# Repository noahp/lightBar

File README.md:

# lightBar
  
Basic serial addressable WS2812B RGB LED banner. Comprised of multiple 12x7 modules.

# hardware
Ordered the boards from dirtypcbs.com, $25 shipped. I received 11 boards (1 bonus!), 22 days turn, pretty nice.  
The basic module contains 84 LEDs arranged in 7 rows of 12 each, and is designed to display 2 monospaced 5x7 pixel characters.  
Several 2-character modules can be connected together to create the full display.  

## schematic
[pdf view](https://github.com/noahp/lightBar/raw/master/hw/lightBar.pdf)

## pcb renders

# software
My plan is to use some Cortex-M processor on the strip itself to do the real-time LED control (framebuffer + SPI transmission). Probably an ESP8266 wifi module (ESP-12) will be used as the interface for setting the displayed data.  
Some ideas-  
- get internet time/date and display it
- display weather, possibly using a gradient over the text background showing temperature/precip conditions

I'm thinking some simple description language (maybe JSON format) to transmit the content from the ESP8266 to the LED controller. Something that can describe text content and position, bitmaps, maybe transparency. The LED controller would parse this data into its bitmapped frame buffer and print it on the display.

For operation of the ESP8266, flow would be like this-  
`wakeup->connect to saved access point credentials (lua file system)`  
`    ->success, get time and date and weather information->sleep`  
`    ->failure after few seconds, switch to access point mode and serve simple web page form with 2 fields, for ssid + key->if HTTP POSTs new credentials->back to start (try to connect)`

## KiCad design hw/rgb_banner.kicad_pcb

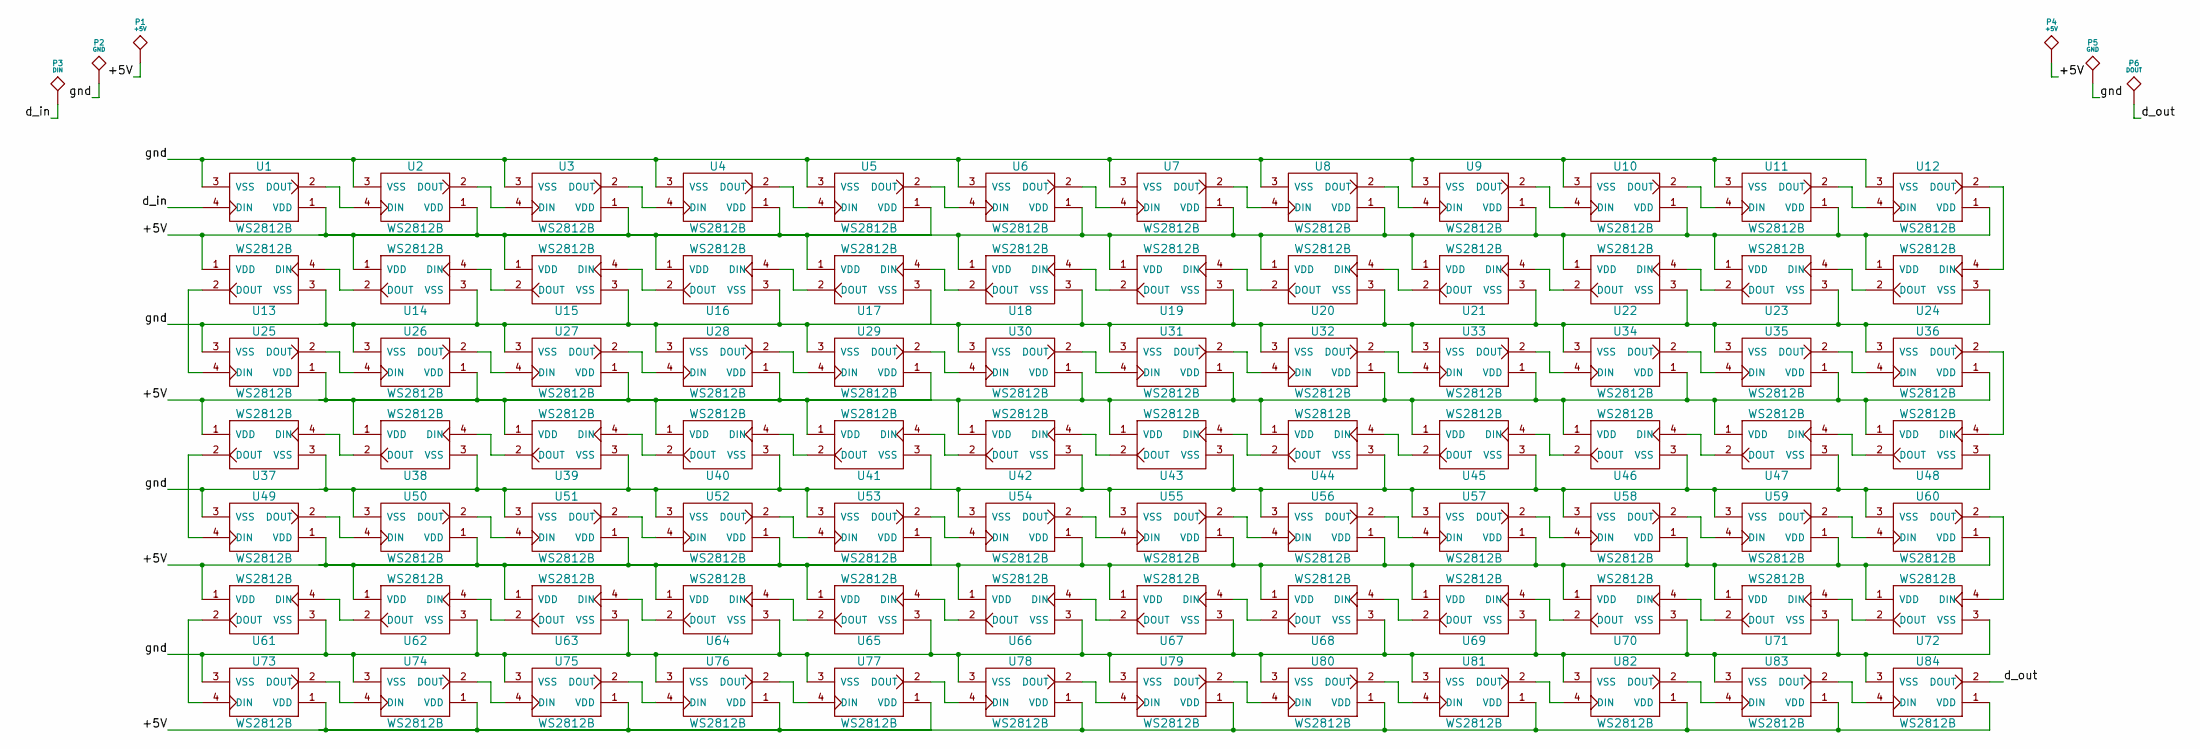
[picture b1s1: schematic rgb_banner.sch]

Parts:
P1, P4: +5V; TEST_0.100
P2, P5: GND; TEST_0.100
P3: DIN; TEST_0.100
P6: DOUT; TEST_0.100
U1, U2, U3, U4, U5, U6, U7, U8, U9, U10, U11, U12, U13, U14, U15, U16, U17, U18, U19, U20, U21, U22, U23, U24, U25, U26, U27, U28, U29, U30, U31, U32, U33, U34, U35, U36, U37, U38, U39, U40, U41, U42, U43, U44, U45, U46, U47, U48, U49, U50, U51, U52, U53, U54, U55, U56, U57, U58, U59, U60, U61, U62, U63, U64, U65, U66, U67, U68, U69, U70, U71, U72, U73, U74, U75, U76, U77, U78, U79, U80, U81, U82, U83, U84: WS2812B; WS2812B_SMD_5050

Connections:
/+5V: P1.1, P4.1, U1.1 (VDD), U2.1 (VDD), U3.1 (VDD), U4.1 (VDD), U5.1 (VDD), U6.1 (VDD), U7.1 (VDD), U8.1 (VDD), U9.1 (VDD), U10.1 (VDD), U11.1 (VDD), U12.1 (VDD), U13.1 (VDD), U14.1 (VDD), U15.1 (VDD), U16.1 (VDD), U17.1 (VDD), U18.1 (VDD), U19.1 (VDD), U20.1 (VDD), U21.1 (VDD), U22.1 (VDD), U23.1 (VDD), U24.1 (VDD), U25.1 (VDD), U26.1 (VDD), U27.1 (VDD), U28.1 (VDD), U29.1 (VDD), U30.1 (VDD), U31.1 (VDD), U32.1 (VDD), U33.1 (VDD), U34.1 (VDD), U35.1 (VDD), U36.1 (VDD), U37.1 (VDD), U38.1 (VDD), U39.1 (VDD), U40.1 (VDD), U41.1 (VDD), U42.1 (VDD), U43.1 (VDD), U44.1 (VDD), U45.1 (VDD), U46.1 (VDD), U47.1 (VDD), U48.1 (VDD), U49.1 (VDD), U50.1 (VDD), U51.1 (VDD), U52.1 (VDD), U53.1 (VDD), U54.1 (VDD), U55.1 (VDD), U56.1 (VDD), U57.1 (VDD), U58.1 (VDD), U59.1 (VDD), U60.1 (VDD), U61.1 (VDD), U62.1 (VDD), U63.1 (VDD), U64.1 (VDD), U65.1 (VDD), U66.1 (VDD), U67.1 (VDD), U68.1 (VDD), U69.1 (VDD), U70.1 (VDD), U71.1 (VDD), U72.1 (VDD), U73.1 (VDD), U74.1 (VDD), U75.1 (VDD), U76.1 (VDD), U77.1 (VDD), U78.1 (VDD), U79.1 (VDD), U80.1 (VDD), U81.1 (VDD), U82.1 (VDD), U83.1 (VDD), U84.1 (VDD)
/d_in: P3.1, U1.4 (DIN)
/d_out: P6.1, U84.2 (DOUT)
/gnd: P2.1, P5.1, U1.3 (VSS), U2.3 (VSS), U3.3 (VSS), U4.3 (VSS), U5.3 (VSS), U6.3 (VSS), U7.3 (VSS), U8.3 (VSS), U9.3 (VSS), U10.3 (VSS), U11.3 (VSS), U12.3 (VSS), U13.3 (VSS), U14.3 (VSS), U15.3 (VSS), U16.3 (VSS), U17.3 (VSS), U18.3 (VSS), U19.3 (VSS), U20.3 (VSS), U21.3 (VSS), U22.3 (VSS), U23.3 (VSS), U24.3 (VSS), U25.3 (VSS), U26.3 (VSS), U27.3 (VSS), U28.3 (VSS), U29.3 (VSS), U30.3 (VSS), U31.3 (VSS), U32.3 (VSS), U33.3 (VSS), U34.3 (VSS), U35.3 (VSS), U36.3 (VSS), U37.3 (VSS), U38.3 (VSS), U39.3 (VSS), U40.3 (VSS), U41.3 (VSS), U42.3 (VSS), U43.3 (VSS), U44.3 (VSS), U45.3 (VSS), U46.3 (VSS), U47.3 (VSS), U48.3 (VSS), U49.3 (VSS), U50.3 (VSS), U51.3 (VSS), U52.3 (VSS), U53.3 (VSS), U54.3 (VSS), U55.3 (VSS), U56.3 (VSS), U57.3 (VSS), U58.3 (VSS), U59.3 (VSS), U60.3 (VSS), U61.3 (VSS), U62.3 (VSS), U63.3 (VSS), U64.3 (VSS), U65.3 (VSS), U66.3 (VSS), U67.3 (VSS), U68.3 (VSS), U69.3 (VSS), U70.3 (VSS), U71.3 (VSS), U72.3 (VSS), U73.3 (VSS), U74.3 (VSS), U75.3 (VSS), U76.3 (VSS), U77.3 (VSS), U78.3 (VSS), U79.3 (VSS), U80.3 (VSS), U81.3 (VSS), U82.3 (VSS), U83.3 (VSS), U84.3 (VSS)
unnamed: U1.2 (DOUT), U2.4 (DIN)
unnamed: U2.2 (DOUT), U3.4 (DIN)
unnamed: U3.2 (DOUT), U4.4 (DIN)
unnamed: U4.2 (DOUT), U5.4 (DIN)
unnamed: U5.2 (DOUT), U6.4 (DIN)
unnamed: U6.2 (DOUT), U7.4 (DIN)
unnamed: U7.2 (DOUT), U8.4 (DIN)
unnamed: U8.2 (DOUT), U9.4 (DIN)
unnamed: U10.2 (DOUT), U11.4 (DIN)
unnamed: U9.2 (DOUT), U10.4 (DIN)
unnamed: U11.2 (DOUT), U12.4 (DIN)
unnamed: U12.2 (DOUT), U24.4 (DIN)
unnamed: U13.2 (DOUT), U25.4 (DIN)
unnamed: U13.4 (DIN), U14.2 (DOUT)
unnamed: U14.4 (DIN), U15.2 (DOUT)
unnamed: U15.4 (DIN), U16.2 (DOUT)
unnamed: U16.4 (DIN), U17.2 (DOUT)
unnamed: U17.4 (DIN), U18.2 (DOUT)
unnamed: U18.4 (DIN), U19.2 (DOUT)
unnamed: U19.4 (DIN), U20.2 (DOUT)
unnamed: U20.4 (DIN), U21.2 (DOUT)
unnamed: U21.4 (DIN), U22.2 (DOUT)
unnamed: U22.4 (DIN), U23.2 (DOUT)
unnamed: U23.4 (DIN), U24.2 (DOUT)
unnamed: U25.2 (DOUT), U26.4 (DIN)
unnamed: U26.2 (DOUT), U27.4 (DIN)
unnamed: U27.2 (DOUT), U28.4 (DIN)
unnamed: U28.2 (DOUT), U29.4 (DIN)
unnamed: U29.2 (DOUT), U30.4 (DIN)
unnamed: U30.2 (DOUT), U31.4 (DIN)
unnamed: U31.2 (DOUT), U32.4 (DIN)
unnamed: U32.2 (DOUT), U33.4 (DIN)
unnamed: U33.2 (DOUT), U34.4 (DIN)
unnamed: U34.2 (DOUT), U35.4 (DIN)
unnamed: U35.2 (DOUT), U36.4 (DIN)
unnamed: U36.2 (DOUT), U48.4 (DIN)
unnamed: U37.2 (DOUT), U49.4 (DIN)
unnamed: U37.4 (DIN), U38.2 (DOUT)
unnamed: U38.4 (DIN), U39.2 (DOUT)
unnamed: U39.4 (DIN), U40.2 (DOUT)
unnamed: U40.4 (DIN), U41.2 (DOUT)
unnamed: U41.4 (DIN), U42.2 (DOUT)
unnamed: U42.4 (DIN), U43.2 (DOUT)
unnamed: U43.4 (DIN), U44.2 (DOUT)
unnamed: U44.4 (DIN), U45.2 (DOUT)
unnamed: U45.4 (DIN), U46.2 (DOUT)
unnamed: U46.4 (DIN), U47.2 (DOUT)
unnamed: U47.4 (DIN), U48.2 (DOUT)
unnamed: U49.2 (DOUT), U50.4 (DIN)
unnamed: U50.2 (DOUT), U51.4 (DIN)
unnamed: U51.2 (DOUT), U52.4 (DIN)
unnamed: U52.2 (DOUT), U53.4 (DIN)
unnamed: U53.2 (DOUT), U54.4 (DIN)
unnamed: U54.2 (DOUT), U55.4 (DIN)
unnamed: U55.2 (DOUT), U56.4 (DIN)
unnamed: U56.2 (DOUT), U57.4 (DIN)
unnamed: U57.2 (DOUT), U58.4 (DIN)
unnamed: U58.2 (DOUT), U59.4 (DIN)
unnamed: U59.2 (DOUT), U60.4 (DIN)
unnamed: U60.2 (DOUT), U72.4 (DIN)
unnamed: U61.2 (DOUT), U73.4 (DIN)
unnamed: U61.4 (DIN), U62.2 (DOUT)
unnamed: U62.4 (DIN), U63.2 (DOUT)
unnamed: U63.4 (DIN), U64.2 (DOUT)
unnamed: U64.4 (DIN), U65.2 (DOUT)
unnamed: U65.4 (DIN), U66.2 (DOUT)
unnamed: U66.4 (DIN), U67.2 (DOUT)
unnamed: U67.4 (DIN), U68.2 (DOUT)
unnamed: U68.4 (DIN), U69.2 (DOUT)
unnamed: U69.4 (DIN), U70.2 (DOUT)
unnamed: U70.4 (DIN), U71.2 (DOUT)
unnamed: U71.4 (DIN), U72.2 (DOUT)
unnamed: U73.2 (DOUT), U74.4 (DIN)
unnamed: U74.2 (DOUT), U75.4 (DIN)
unnamed: U75.2 (DOUT), U76.4 (DIN)
unnamed: U76.2 (DOUT), U77.4 (DIN)
unnamed: U77.2 (DOUT), U78.4 (DIN)
unnamed: U78.2 (DOUT), U79.4 (DIN)
unnamed: U79.2 (DOUT), U80.4 (DIN)
unnamed: U80.2 (DOUT), U81.4 (DIN)
unnamed: U81.2 (DOUT), U82.4 (DIN)
unnamed: U82.2 (DOUT), U83.4 (DIN)
unnamed: U83.2 (DOUT), U84.4 (DIN)

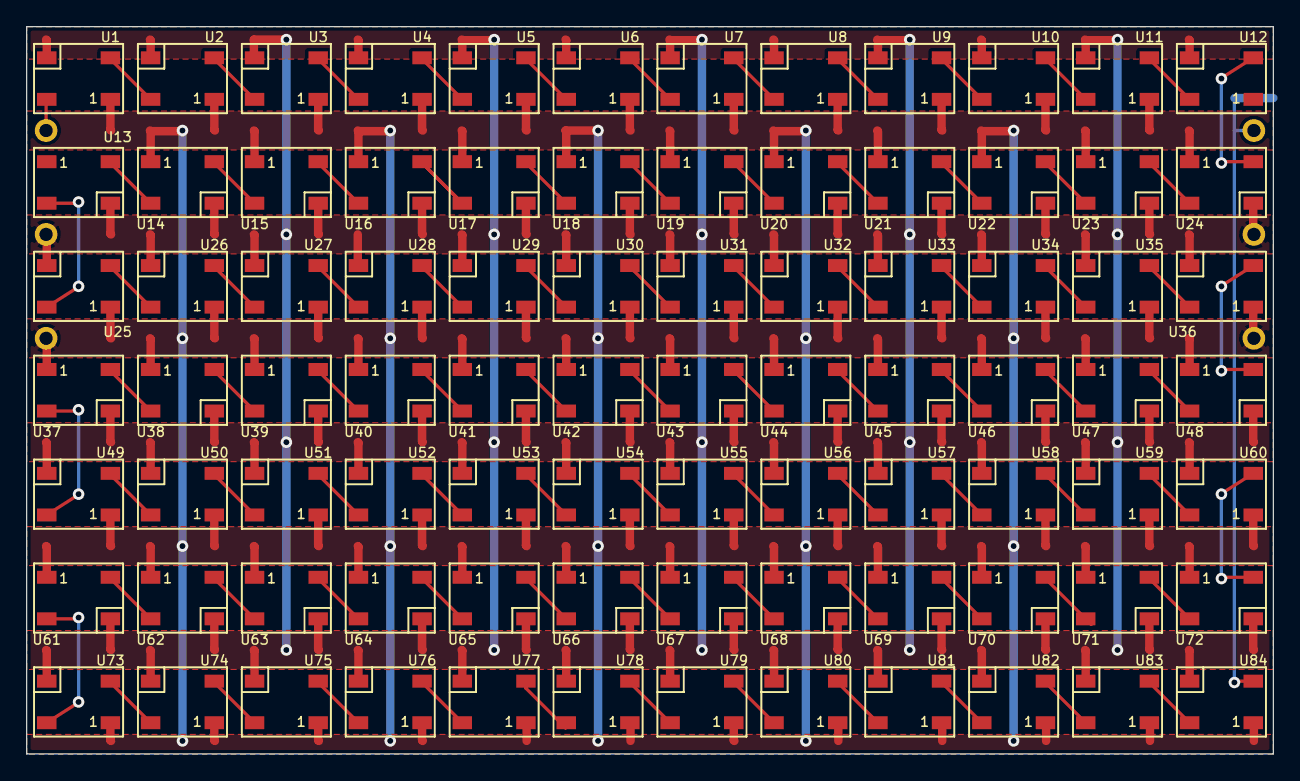
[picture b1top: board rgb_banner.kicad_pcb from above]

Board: 2 copper layers, 96.0 x 56.0 mm, 90 parts (0 on the bottom side), 87 nets.

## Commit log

2015-06-01 add kicad project + sch
2015-06-01 add submodule kicadlib
2015-06-01 add 4x ws2812b to schematic
2015-06-01 add pcb
2015-06-01 schematic pretty much done, start layout
2015-06-01 new version of kicalib with the correct module for
2015-06-01 try to remove submodule
2015-06-01 add submodule back
2015-06-01 update to latest master
2015-06-01 add pdf
2015-06-01 work some on pcb, add trial image and link to 200 pcs ws2812b on aliexpress.
2015-06-01 start consolidating schematic
2015-06-03 pcb layout. zones not working.
2015-06-03 add test gerbers
2015-06-03 zones not working
2015-06-03 zone fill by setting to no_net, filling, then setting correct net.
2015-06-03 remove "special" library??
2015-06-10 work on pcb
2015-06-10 add some example bit patterns
2015-06-10 add gerbers, update the mockups a bit
2015-06-10 add silks to the back
2015-06-17 renames
2015-06-18 replot
2015-06-19 save gerbers used in v0.1 dirtypcbs order
2015-06-22 add example file for win32 console colors
2015-06-23 fix some errors in the pcb- unconnected pads >_< change version silk to 2
2015-07-13 add rgb blink sw project files
2015-07-13 remove warning in usb code add 84-led buffer and fill them all with the same color/brightness
2015-07-14 finish scan and increment modes. add all on mode.
2015-07-15 scanPos to unsigned int so we don't set the previous led to zero and clearing scan mode will set the first led on
2015-07-15 save test code
2015-07-15 rework how config works; now hit ctrl-q then the config values
2015-07-15 add font files
2015-07-15 start working on text display. lots to do.
2015-07-15 clear character working now
2015-07-15 ok fonts now
2015-07-16 add pcb renders from dirtypcbs
2015-07-16 change driver to x,y addressing, much better
2015-07-17 remove scan option, scroll opposite direction.
2015-07-17 add toggle scan back
2015-07-17 don't require usb to be connected to run
2015-07-20 add test mode (all on)
2015-07-22 mild rearchitect, sub out rgb management to separate file
2015-07-22 try to get uart0 working, no dice
2015-07-22 fix pinouts for uart0 init, works now.
2015-07-22 process input from UART0 same as USB
2015-07-22 getting there. the bannerizing needs some work.
2015-07-23 double wide!
2015-08-04 set test mode to default, fix some errors, add 2nd panel
2015-10-21 add pumpkin image
2015-10-22 some changes to get scrolling to work more correctly. not perfect but functional. seasonal too!
2016-04-25 up to 3 panels
2016-04-25 rework some stuff. add sbrk implementation. clock mode sortof.
